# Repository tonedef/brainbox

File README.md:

# Important Notice
I am not a physician and make no guarantees about this device's effectiveness, safety, or intended function. It uses pulsing light and sound, which may pose risks for individuals with epilepsy or other neurological conditions. Anyone choosing to build or use this device, in whole or in part, should consult their physician beforehand. By engaging with this device or any related information, you accept full responsibility for all risks. Always discuss medical concerns with your doctor first.

# What is Memini?
Memini is a simple device that produces 40Hz audio and light pulses designed to delay and slow the progression of Alzheimer's/dementia. It's based on promising research done at MIT: 
https://news.mit.edu/2022/small-studies-40hz-sensory-stimulation-confirm-safety-suggest-alzheimers-benefits-1213 (again, I cannot ensure that this will happen.  There are ongoing clinic trials for this, and I have no guarantee that the designs here will be able to achieve that)

It's meant to be as simple as possible for anyone to use. A dimmer to control how bright the light is, a volume control for the sound, and a single button to start/stop the device. It also has a web interface accessible thru WiFi, and the code can be upgraded/modified to support all kinds of things such as:
- making it an alarm clock, so that it runs without user intervention
- tracking usage
- playing reminders for other mental activities
- Repurposing for anything else that could use a couple of buttons and a mono audio output

The MCU being used is a Wemos S2 mini board. While you can use a Wemos C3, or an older D1 (code changes required), the S2 is ideal, as it includes a DAC output which makes it easy to modify the existing on/off square wave audio pulse to support significantly more audio options thru software upgrades.

It's designed using pre-built dev boards and a few through-hole components to make it easy for hobbyists to make. The most challanging thing to build will be the housing, but really anything box like can be used for that.

# Getting started
Aquire the components.

## Electronic component BOM

- 1x PCB board. Send the grb_v_x_x.zip to your PCB mfg. This is the latest confirmed [build](https://github.com/tonedef/Memini/blob/main/KiCad/40Hz_S2/grb_v_0_3.zip)
- 1x [Wemos S2 mini](https://www.amazon.com/HiLetgo-ESP32-S2FN4R2-ESP32-S2-Type-C-Connect/dp/B0B291LZ99)
- 1x  N-Channel logic level MOSFET [CSD19531KCS](https://www.digikey.com/en/products/detail/texas-instruments/CSD19531KCS/4437459). If you're using a short LED strip (< 400mm), you can get away with generic MOSFETs, like the ubiquitous [IRF540](https://www.amazon.com/dp/B0CBKGPJML), which I've tried sucessfully.
- 1x 100 Ohm resistor a [kit](https://www.amazon.com/Resistors-Assortment-Electronic-Components-Experiments/dp/B09SFCF5XY/) is probably the best bet for this if you don't have one already
- 1x 10k Ohm resistor a [kit](https://www.amazon.com/Resistors-Assortment-Electronic-Components-Experiments/dp/B09SFCF5XY/) is probably the best bet for this if you don't have one already
- 1x 1n4007 Diode. Again, a [kit](https://www.amazon.com/HiLetgo-100pcs-Schottky-Rectifier-Assorted/dp/B07VHMCJK1/) if you don't have one already
- 1x 10k Ohm 15mm PCB vertical [potentiometer](https://www.amazon.com/dp/B0DN1DHWLR).
- 1x 20mm Rotary [encoder](https://www.amazon.com/dp/B07D3DF8TK) (with or without switch). 
- 1x 0.96in 4 pin [I2C display](https://www.amazon.com/MakerFocus-Display-Communication-SSD1315-Raspberry/dp/B0DR2CMYGM)
- 1x PAM8302 [audio dev board](https://www.amazon.com/Audio-Development-Tools-Adafruit-Amplifier/dp/B00PY2YSI4)
- 5V [LED strip](https://www.amazon.com/dp/B0DPKMQNJJ) (pay attention to the Voltage, most are 12V). You can use any color, but I'd recommend a warm white like 3000K.
- 2x 6×6×9mm [Momentary Tactile Tact Push Button Switches](https://www.amazon.com/dp/B07CGCPGPT?th=1)
- 1x Small 4 Ohm [speaker](https://www.amazon.com/dp/B0CCP2Q168)
- 1x [5V power supply](https://www.amazon.com/100-240V-Extension-Replacement-5-5x2-5mm-Security/dp/B0DGFSQS97) walwart
- 1x DC [jack](https://www.amazon.com/dp/B07CTCLKPP) that fits your 5V walwart
- 2x M2x6mm standoffs. A [kit](https://www.amazon.com/300pcs-Standoff-Column-Spacer-Assortment/dp/B07B9X1KY6/) is good, if you don't have one already.
- Assorted 2.54mm male and female [headers](https://www.amazon.com/dp/B0774VBJ3J) (most/all of these should already be included in the components above). You can of course use [JTS-XH](https://www.amazon.com/Taiss-560PCS-Connector-Adapter-Housing/dp/B09ZTWCZ3K) connectors for the power in, LED out, and  audio out, or just wire them directly.
 
 ## Case
 There's plenty of ways to do this. The easiest is to just a get a cast acrylic box that's roughly 4"x4"x4" and has roughly 1/8" (3mm) thick walls. I simply made boxes out of wood I had lying around, and grabbed a cheap piece of 1/8" scrap cast acrylic from TAP Plastics for the face plate. Cast acrylic usually has a paper backing as opposed to a plastic film. Cast acrylic is generally easier to machine.

 # Assembly
 ## software
 You will need to know how to connect your Wemos S2 to your PC and upload the code to it. There are plenty of tutorials on how to do this. The board needs to be in the [DFU mode](https://www.wemos.cc/en/latest/tutorials/s2/get_started_with_arduino_s2.html) to get picked up, and you need the espressif boards in your Arduino IDE, along with a bunch of libraries:
 - ESP32 boards [installation](https://randomnerdtutorials.com/installing-the-esp32-board-in-arduino-ide-windows-instructions/)
 - ezButton (library from ArduinoGetStarted.com)
 - ESP Rotary (library from Lennart Hennigs)
 - Adafruit_GFX (library from Adafruit)
 - Adafruit_SSD1306 (library from Adafruit)
  
  Libraries are installed thru the Arudino IDE interface. It's been a while since I installed the things I need, so my appologies if I've missed anything. If you get errors, it should point to what's missing, and you'll have to  look for it and install the library.

  ## hardware (main board)
  - install the female headers for the Wemos board
  - dry fit the male pins to the audio dev board and the PCB (don't solder just yet)
  - solder the male pins to all the dev boards (Wemos, audio, and display). DON'T solder to any of these to the PCB just yet, but do dry fit them to make sure the pins are properly aligned and adjust if needed.
  - if your using connectors for the power in, audio out, and LED out, solder them now
  - solder all the remaining components to the PCB except for the display
  - attach the standoffs to the display.
  - As the OLED 0.96 displays aren't fully standardized on pin placement and mounting holes, the PCB has generous sized mounting holes and pin pads. Fit the display on the PCB and align it.
  - screw in the display's attached standoffs to the PCB
  - keeping the display parallel to the PCB, solder the display pins to the PCB
 
 ## hardware (DC jack, LED, and speaker)

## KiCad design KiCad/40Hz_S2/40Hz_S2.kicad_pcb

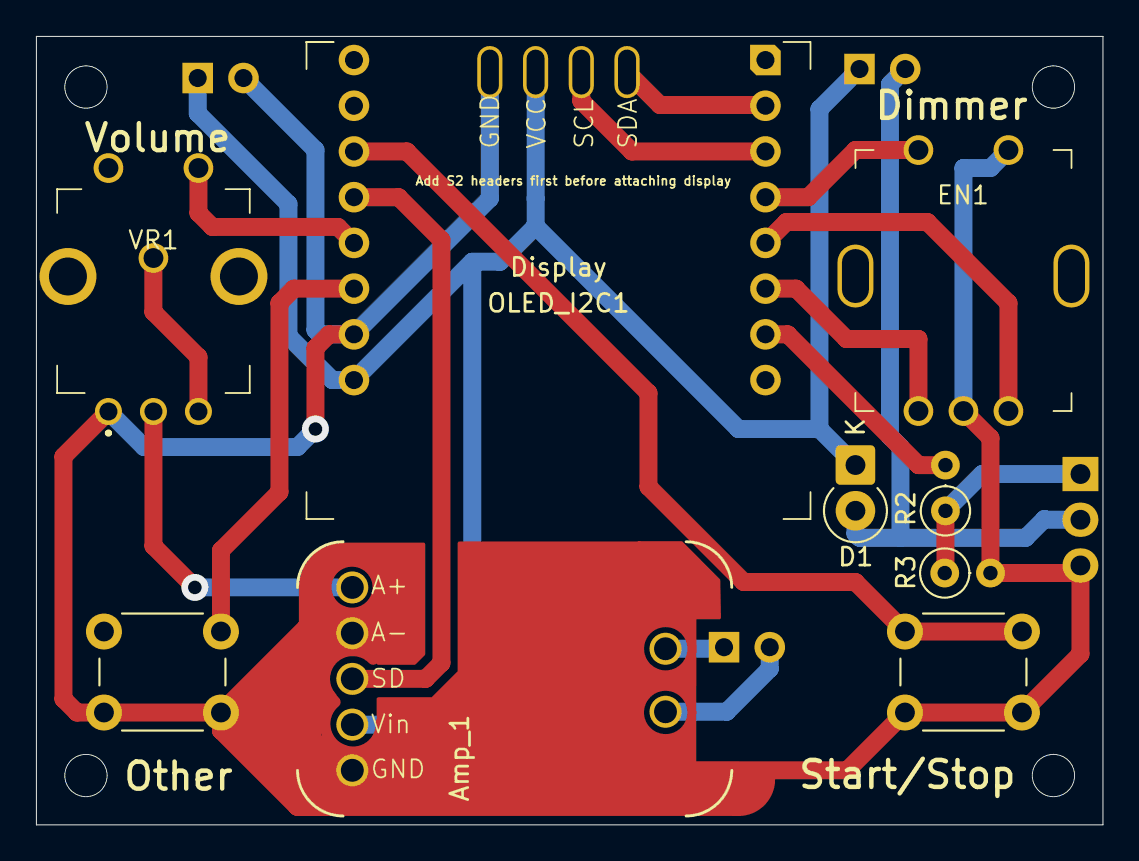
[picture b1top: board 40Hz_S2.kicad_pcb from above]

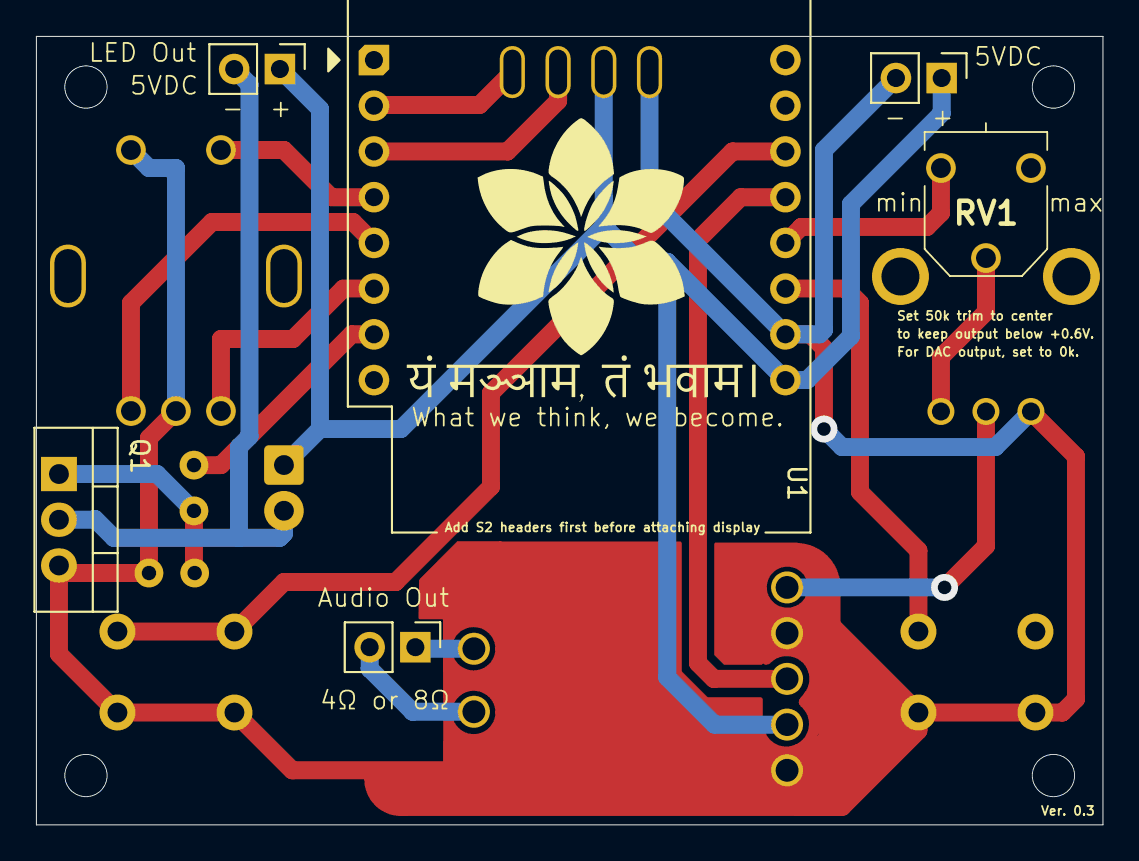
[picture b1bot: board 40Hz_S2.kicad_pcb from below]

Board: 2 copper layers, 59.2 x 43.8 mm, 15 parts (6 on the bottom side), 18 nets.

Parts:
Amp_1: PAM8302_adafruit
D1: 1N4007; D_DO-41_SOD81_P2.54mm_Vertical_KathodeUp
EN1: Encoder; encoder_20mm_switch
J1: PWR; PinHeader_1x02_P2.54mm_Vertical
J2: Audio; PinHeader_1x02_P2.54mm_Vertical
J3: LED; PinHeader_1x02_P2.54mm_Vertical
OLED_I2C1: Display; OLED_display_I2C_0_96in
Q1: CSD19531KCS; TO-220-3_Vertical
R2: 100; R_Axial_DIN0207_L6.3mm_D2.5mm_P2.54mm_Vertical
R3: 10K; R_Axial_DIN0207_L6.3mm_D2.5mm_P2.54mm_Vertical
RV1: R_Potentiometer_Trim_US; 3306F1103
U1: WeMos_S2_mini; WEMOS_S2_mini_no_inner_row
VR1: 10K Pot; potentiometer_vert_no_switch
other1: Start/Stop; SW_PUSH_6mm_H9.5mm
start/stop1: Start/Stop; SW_PUSH_6mm_H9.5mm

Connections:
5V: Amp_1.4 (Vin), D1.1 (K), J1.1, J3.1, OLED_I2C1.Vcc, U1.9 (VBUS)
Audio: RV1.3, U1.12 (IO18)
Btn1: U1.14 (IO35), start/stop1.1
Btn2: EN1.1, U1.4 (IO7)
Btn3: U1.11 (IO16), other1.1
Enc_A: EN1.A1 (A), U1.6 (IO11)
Enc_B: EN1.B1 (B), U1.5 (IO9)
GND: Amp_1.2 (A-), Amp_1.5 (GND), EN1.2, EN1.GND, J1.2, OLED_I2C1.GND, Q1.3 (S), R3.2, U1.10 (GND), VR1.1, other1.2, start/stop1.2
LED: R2.2, U1.7 (IO12)
unnamed: Amp_1.1 (A+), VR1.2
unnamed: Amp_1.7 (SPK+), J2.2
unnamed: Amp_1.6 (SPK-), J2.1
unnamed: D1.2 (A), J3.2, Q1.2 (D)
unnamed: Q1.1 (G), R2.1, R3.1
unnamed: RV1.2, VR1.3
SCL: OLED_I2C1.SCL, U1.3 (IO5)
SD: Amp_1.3 (SD), U1.13 (IO33)
SDA: OLED_I2C1.SDA, U1.2 (IO3)

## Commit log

2025-05-07 work in progress. add license
2025-05-09 working code
2025-05-09 reorg code
2025-05-09 add file structure
2025-05-16 Revamp code. Restructure. Add KiCad files
2025-05-30 updated grp files
2025-05-30 ignore backups
2025-05-30 cleanup
2025-05-30 rename grb files with current ver no.
2025-05-30 update BOM
2025-05-30 update structure
2025-05-30 Update links in readme
2025-05-30 add image
2025-06-10 update README.md with new name
2025-06-12 rm .pio.nosync
2025-06-12 rm dead code
2025-06-17 bug fixes, refactor and begin cleanup
2025-06-17 Code cleanup
2025-06-18 Small cleanups. Trying to add unit tests
2025-06-18 Add notes for test. Change defaults
2025-06-19 updated instructions
